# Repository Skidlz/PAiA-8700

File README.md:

# PAiA-8700
A redraw of the PAiA 8700 music computer in Eagle CAD</br>
Also includes:</br>
 - Python scripts for converting to and from tape dump format

 ##### TAPE PROGRAMS #####
 - [**Echo**](Tape%20Programs/Echo/) listing/binary/tape dump
 - [**Orgasmatronic Glide (O-Glide)**](Tape%20Programs/O-Glide) listing/binary/tape dump
 - [**Poly-Split**](Tape%20Programs/Poly-Split/) listing/binary/tape dump
 - [**Poly**](Tape%20Programs/Poly/) listing/source/binary/audio file
 - [**Seque**](Tape%20Programs/Seque/) listing/binary/tape dump
 - [**Pink Tunes**](Tape%20Programs/Pink%20Tunes/) listing/source/binary/tape dump
 - [**Pink Music**](Tape%20Programs/Pink%20Music/) listing/source/binary/audio file
 - [**DrumSys 0.6**](Tape%20Programs/DRUMSYS%2006/) listing/source/binary/audio file
 - [**Shazam 0.1**](Tape%20Programs/SHAZAM/) listing/source/binary/audio file
 - [**Micro-Drums 2.1**](Tape%20Programs/Micro-Drums/) listing/source/binary/audio file
 - [**Chameleon**](Tape%20Programs/Chameleon) listing/source/binary
 - Test programs source/binary/tape dump

##### EPROM PROGRAMS #####
 - [**PIEBUG**](EPROM%20Programs/PIEBUG) listing/binary/source
 - [**POT-SHOT**](EPROM%20Programs/POT-SHOT) listing/binary/source
 - [**MUS-1**](EPROM%20Programs/MUS-1) listing/source/binary
 
##### EXTRAS #####
 - memory map
 
 - 600DPI scan on the Seque overlay

##### NOTES #####
.asm files can be assembled with [Frank's Cross Assembler (AS65)](http://www.kingswood-consulting.co.uk/assemblers/).

##### BUGS #####
###### DrumSys ######
The original code listing for DrumSys contains an error in the code/data alginment. Two versions are included here, and they correct the error in opposite ways. One shifts the data, while the other shifts the code.

###### Echo ######
Echo has a relative branch that is out of range. At address $080 is "beq STAR". STAR, being at $000, is a byte too far away, and the branch instead points to $100. This has not been corrected. Adding a "jmp STAR" at address $100 is a possible fix to the issue.

.jpg)

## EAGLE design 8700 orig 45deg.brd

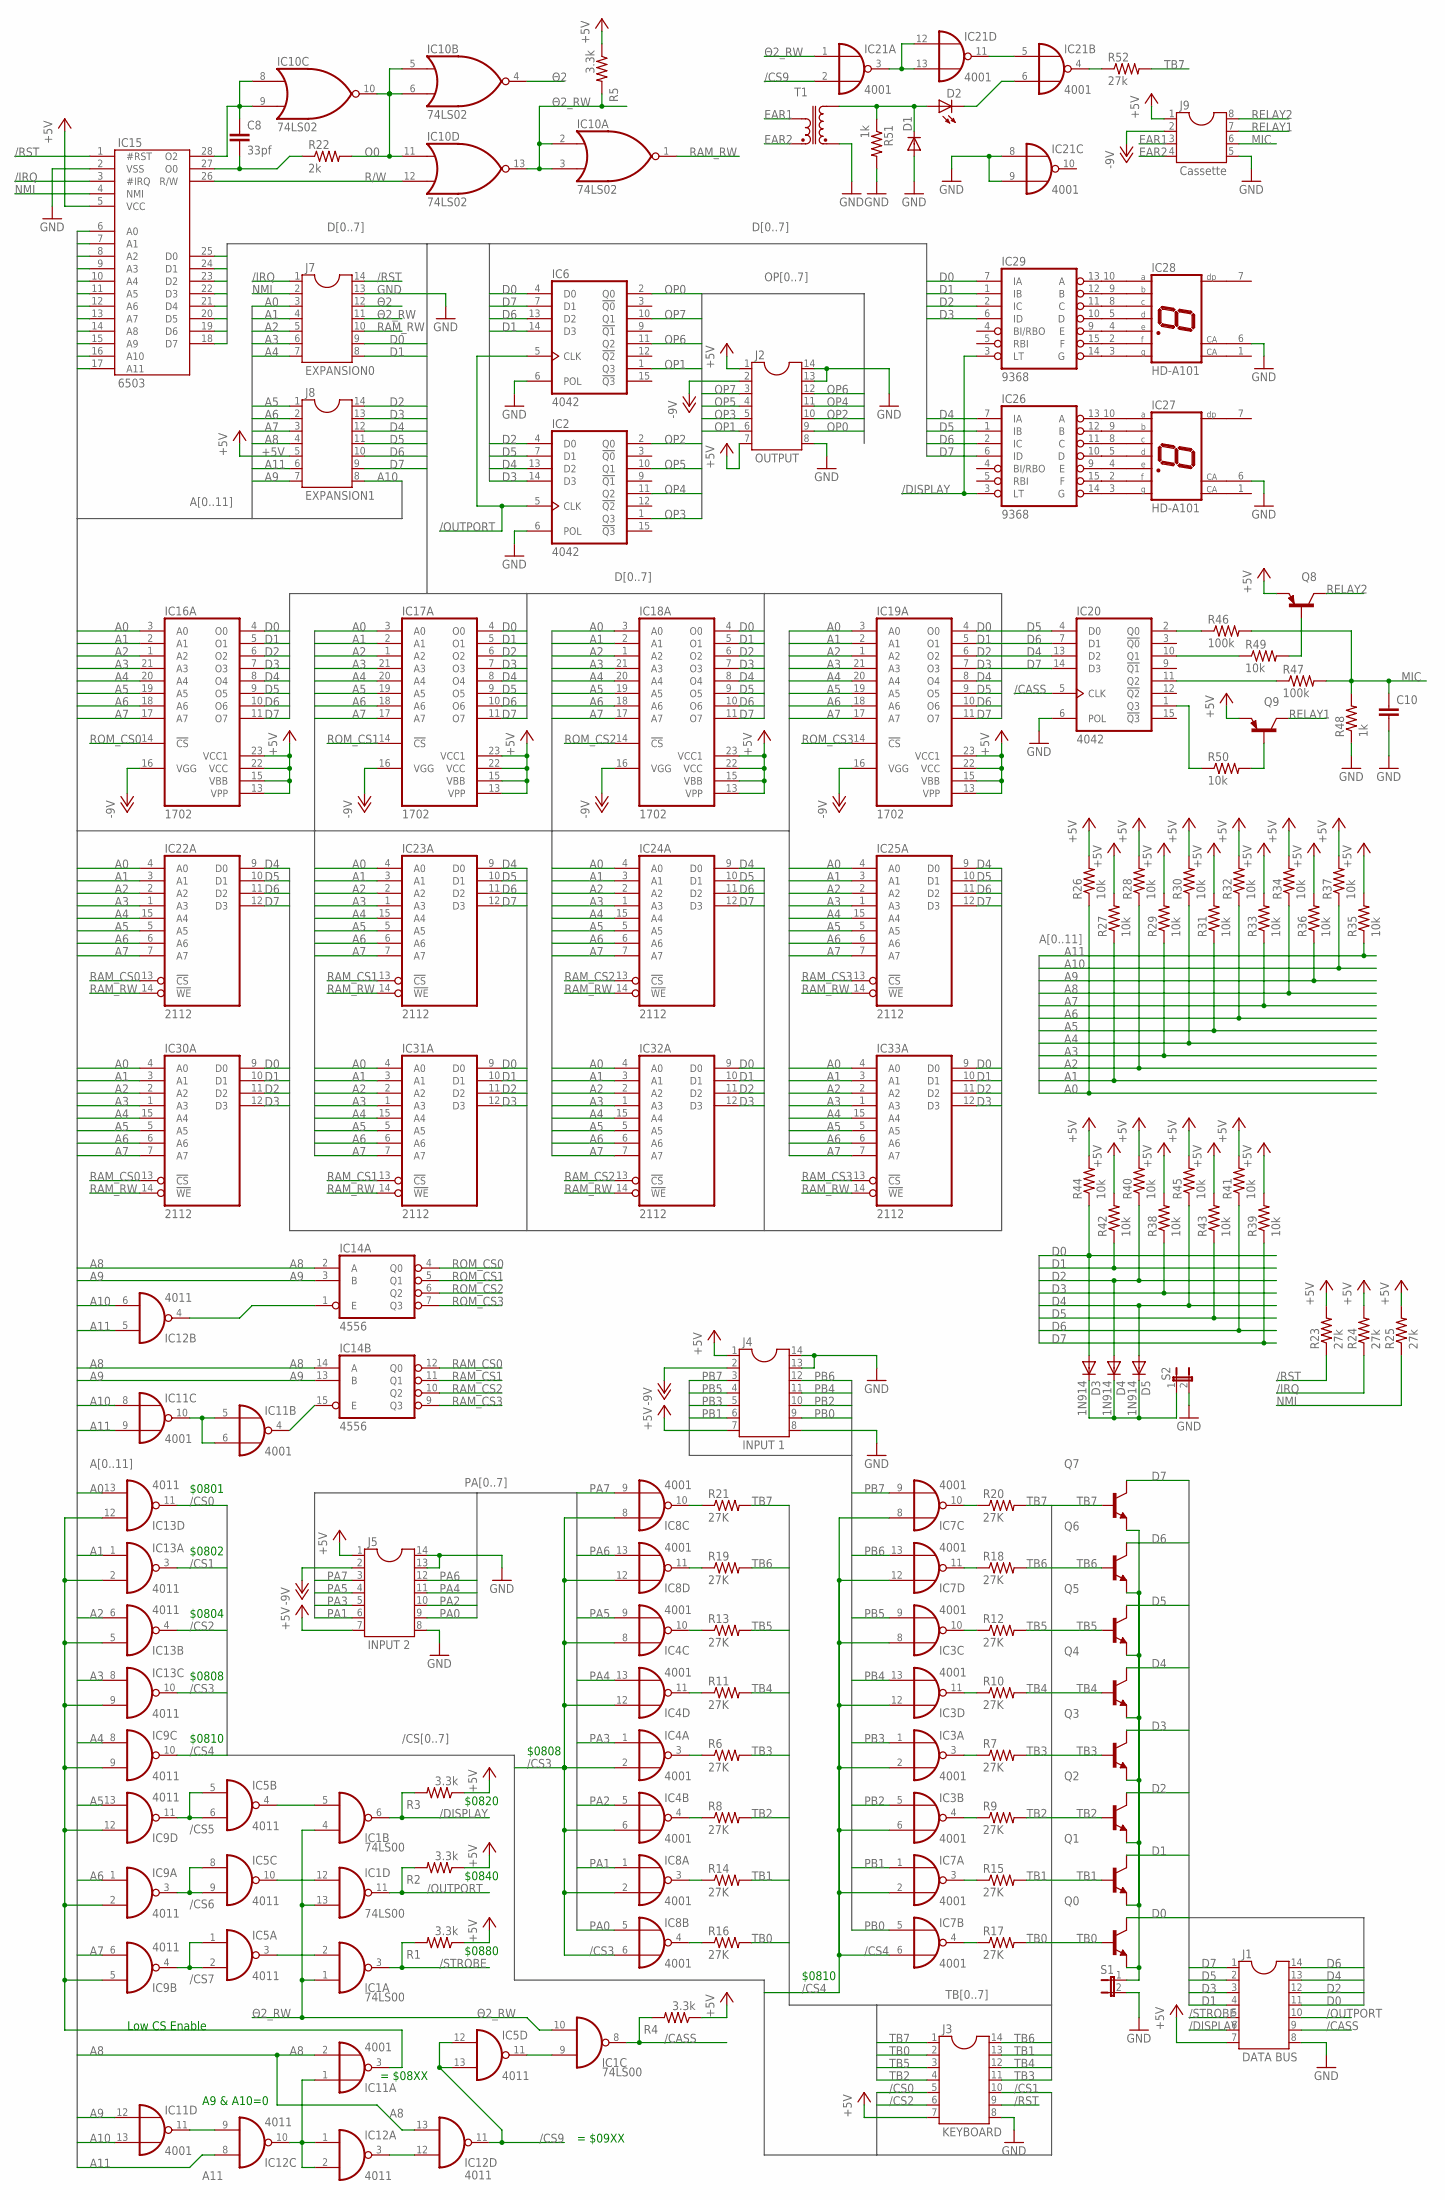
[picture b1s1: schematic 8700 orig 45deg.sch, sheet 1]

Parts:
C8: 33pf; C050-025X075
C10: C-EU050-025X075; C050-025X075
D1: DIODE-DO07; DO07
D2: LED3MM
D3, D4, D5: 1N914; DO07
IC1: 74LS00; DIL14
IC2, IC6, IC20: 4042; DIL16
IC3, IC4, IC7, IC8, IC11, IC21: 4001; DIL14
IC5, IC9, IC12, IC13: 4011; DIL14
IC10: 74LS02; DIL14
IC14: 4556; DIL16
IC15: 6503; DIL28-6
IC16, IC17, IC18, IC19: 1702; DIL24
IC22, IC23, IC24, IC25, IC30, IC31, IC32, IC33: 2112; DIL16
IC26, IC29: 9368; DIL16
IC27, IC28: HD-A101; HDSP-A
J1: DATA BUS; DIL14
J2: OUTPUT; DIL14
J3: KEYBOARD; DIL14
J4: INPUT 1; DIL14
J5: INPUT 2; DIL14
J7: EXPANSION0; DIL14
J8: EXPANSION1; DIL14
J9: Cassette; DIL08
Q0, Q1, Q2, Q3, Q4, Q5, Q6, Q7: 2N3904-NPN-TO92-EBC; TO92-EBC
Q8, Q9: 2N3906-PNP-TO92-EBC; TO92-EBC
R1, R2, R3, R4, R5: 3.3k; 0207/10
R6, R7, R8, R9, R10, R11, R12, R13, R14, R15, R16, R17, R18, R19, R20, R21: 27K; 0207/10
R22: 2k; 0207/10
R23, R24, R25, R52: 27k; 0207/10
R26, R27, R28, R29, R30, R31, R32, R33, R34, R35, R36, R37, R38, R39, R40, R41, R42, R43, R44, R45, R49, R50: 10k; 0207/10
R46, R47: 100k; 0207/10
R48, R51: 1k; 0207/10
S1, S2: JUMPER
T1: TRANSF

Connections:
+5V: IC15.5 (VCC), IC16.13 (VPP), IC16.15 (VBB), IC16.22 (VCC), IC16.23 (VCC1), IC17.13 (VPP), IC17.15 (VBB), IC17.22 (VCC), IC17.23 (VCC1), IC18.13 (VPP), IC18.15 (VBB), IC18.22 (VCC), IC18.23 (VCC1), IC19.13 (VPP), IC19.15 (VBB), IC19.22 (VCC), IC19.23 (VCC1), J1.7, J2.1, J2.7, J3.7, J4.1, J4.7, J5.1, J5.7, J8.5, J9.1, Q8.E, Q9.E, R1.1, R2.1, R3.1, R4.1, R5.1, R23.2, R24.2, R25.2, R26.2, R27.2, R28.2, R29.2, R30.2, R31.2, R32.2, R33.2, R34.2, R35.2, R36.2, R37.2, R38.2, R39.2, R40.2, R41.2, R42.2, R43.2, R44.2, R45.2; also elsewhere on the board
-9V: IC16.16 (VGG), IC17.16 (VGG), IC18.16 (VGG), IC19.16 (VGG), J2.2, J4.2, J5.2, J9.2; also elsewhere on the board
/CASS: IC1.8 (O), IC20.5 (CLK), J1.9, R4.2
/CS0: IC13.11 (O), J3.5
/CS1: IC13.3 (O), J3.10
/CS2: IC13.4 (O), J3.6
/CS3: IC4.2 (I1), IC4.6 (I1), IC4.8 (I0), IC4.12 (I0), IC8.2 (I1), IC8.6 (I1), IC8.8 (I0), IC8.12 (I0), IC13.10 (O)
/CS4: IC3.2 (I1), IC3.6 (I1), IC3.8 (I0), IC3.12 (I0), IC7.2 (I1), IC7.6 (I1), IC7.8 (I0), IC7.12 (I0), IC9.10 (O)
/CS5: IC5.5 (I0), IC5.6 (I1), IC9.11 (O)
/CS6: IC5.8 (I0), IC5.9 (I1), IC9.3 (O)
/CS7: IC5.1 (I0), IC5.2 (I1), IC9.4 (O)
/CS9: IC5.12 (I0), IC5.13 (I1), IC12.11 (O), IC21.2 (I1)
/DISPLAY: IC1.6 (O), IC26.3 (LT), IC29.3 (LT), J1.6, R3.2
/IRQ: IC15.3 (#IRQ), J7.1, R24.1
/OUTPORT: IC1.11 (O), IC2.5 (CLK), IC6.5 (CLK), J1.10, R2.2
/RST: IC15.1 (#RST), J3.9, J7.14, R23.1
/STROBE: IC1.3 (O), J1.5, R1.2
A0: IC13.13 (I1), IC15.6 (A0), IC16.3 (A0), IC17.3 (A0), IC18.3 (A0), IC19.3 (A0), IC22.4 (A0), IC23.4 (A0), IC24.4 (A0), IC25.4 (A0), IC30.4 (A0), IC31.4 (A0), IC32.4 (A0), IC33.4 (A0), J7.3, R26.1
A1: IC13.1 (I0), IC15.7 (A1), IC16.2 (A1), IC17.2 (A1), IC18.2 (A1), IC19.2 (A1), IC22.3 (A1), IC23.3 (A1), IC24.3 (A1), IC25.3 (A1), IC30.3 (A1), IC31.3 (A1), IC32.3 (A1), IC33.3 (A1), J7.4, R27.1
A2: IC13.6 (I1), IC15.8 (A2), IC16.1 (A2), IC17.1 (A2), IC18.1 (A2), IC19.1 (A2), IC22.2 (A2), IC23.2 (A2), IC24.2 (A2), IC25.2 (A2), IC30.2 (A2), IC31.2 (A2), IC32.2 (A2), IC33.2 (A2), J7.5, R28.1
A3: IC13.8 (I0), IC15.9 (A3), IC16.21 (A3), IC17.21 (A3), IC18.21 (A3), IC19.21 (A3), IC22.1 (A3), IC23.1 (A3), IC24.1 (A3), IC25.1 (A3), IC30.1 (A3), IC31.1 (A3), IC32.1 (A3), IC33.1 (A3), J7.6, R29.1
A4: IC9.8 (I0), IC15.10 (A4), IC16.20 (A4), IC17.20 (A4), IC18.20 (A4), IC19.20 (A4), IC22.15 (A4), IC23.15 (A4), IC24.15 (A4), IC25.15 (A4), IC30.15 (A4), IC31.15 (A4), IC32.15 (A4), IC33.15 (A4), J7.7, R30.1
A5: IC9.13 (I1), IC15.11 (A5), IC16.19 (A5), IC17.19 (A5), IC18.19 (A5), IC19.19 (A5), IC22.5 (A5), IC23.5 (A5), IC24.5 (A5), IC25.5 (A5), IC30.5 (A5), IC31.5 (A5), IC32.5 (A5), IC33.5 (A5), J8.1, R31.1
A6: IC9.1 (I0), IC15.12 (A6), IC16.18 (A6), IC17.18 (A6), IC18.18 (A6), IC19.18 (A6), IC22.6 (A6), IC23.6 (A6), IC24.6 (A6), IC25.6 (A6), IC30.6 (A6), IC31.6 (A6), IC32.6 (A6), IC33.6 (A6), J8.2, R32.1
A7: IC9.6 (I1), IC15.13 (A7), IC16.17 (A7), IC17.17 (A7), IC18.17 (A7), IC19.17 (A7), IC22.7 (A7), IC23.7 (A7), IC24.7 (A7), IC25.7 (A7), IC30.7 (A7), IC31.7 (A7), IC32.7 (A7), IC33.7 (A7), J8.3, R33.1
A8: IC11.2 (I1), IC12.13 (I1), IC14.2 (A), IC14.14 (A), IC15.14 (A8), J8.4, R34.1
A9: IC11.12 (I0), IC14.3 (B), IC14.13 (B), IC15.15 (A9), J8.7, R36.1
A10: IC11.8 (I0), IC11.13 (I1), IC12.6 (I1), IC15.16 (A10), J8.8, R37.1
A11: IC11.9 (I1), IC12.5 (I0), IC12.8 (I0), IC15.17 (A11), J8.6, R35.1
D0: D3.A, IC6.4 (D0), IC15.25 (D0), IC16.4 (O0), IC17.4 (O0), IC18.4 (O0), IC19.4 (O0), IC29.7 (IA), IC30.9 (D0), IC31.9 (D0), IC32.9 (D0), IC33.9 (D0), J1.11, J7.9, Q0.C, R44.1
D1: IC6.14 (D3), IC15.24 (D1), IC16.5 (O1), IC17.5 (O1), IC18.5 (O1), IC19.5 (O1), IC29.1 (IB), IC30.10 (D1), IC31.10 (D1), IC32.10 (D1), IC33.10 (D1), J1.4, J7.8, Q1.C, R42.1
D2: D4.A, IC2.4 (D0), IC15.23 (D2), IC16.6 (O2), IC17.6 (O2), IC18.6 (O2), IC19.6 (O2), IC29.2 (IC), IC30.11 (D2), IC31.11 (D2), IC32.11 (D2), IC33.11 (D2), J1.12, J8.14, Q2.C, R40.1
D3: IC2.14 (D3), IC15.22 (D3), IC16.7 (O3), IC17.7 (O3), IC18.7 (O3), IC19.7 (O3), IC29.6 (ID), IC30.12 (D3), IC31.12 (D3), IC32.12 (D3), IC33.12 (D3), J1.3, J8.13, Q3.C, R38.1
D4: D5.A, IC2.13 (D2), IC15.21 (D4), IC16.8 (O4), IC17.8 (O4), IC18.8 (O4), IC19.8 (O4), IC20.13 (D2), IC22.9 (D0), IC23.9 (D0), IC24.9 (D0), IC25.9 (D0), IC26.7 (IA), J1.13, J8.12, Q4.C, R45.1
D5: IC2.7 (D1), IC15.20 (D5), IC16.9 (O5), IC17.9 (O5), IC18.9 (O5), IC19.9 (O5), IC20.4 (D0), IC22.10 (D1), IC23.10 (D1), IC24.10 (D1), IC25.10 (D1), IC26.1 (IB), J1.2, J8.11, Q5.C, R43.1
D6: IC6.13 (D2), IC15.19 (D6), IC16.10 (O6), IC17.10 (O6), IC18.10 (O6), IC19.10 (O6), IC20.7 (D1), IC22.11 (D2), IC23.11 (D2), IC24.11 (D2), IC25.11 (D2), IC26.2 (IC), J1.14, J8.10, Q6.C, R41.1
D7: IC6.7 (D1), IC15.18 (D7), IC16.11 (O7), IC17.11 (O7), IC18.11 (O7), IC19.11 (O7), IC20.14 (D3), IC22.12 (D3), IC23.12 (D3), IC24.12 (D3), IC25.12 (D3), IC26.6 (ID), J1.1, J8.9, Q7.C, R39.1
EAR1: J9.3, T1.P$1 (P1)
EAR2: J9.4, T1.P$2 (P2)
GND: C10.2, D1.A, IC2.6 (POL), IC6.6 (POL), IC15.2 (VSS), IC20.6 (POL), IC21.8 (I0), IC21.9 (I1), IC27.6 (CA), IC28.6 (CA), J1.8, J2.8, J2.13, J2.14, J3.8, J4.8, J4.13, J4.14, J5.8, J5.13, J5.14, J7.13, J9.5, R48.1, R51.2, S1.2, S2.2, T1.P$5 (S1); also elsewhere on the board
MIC: C10.1, J9.6, R46.2, R47.2, R48.2
unnamed: C8.1, IC10.8 (I0), IC10.9 (I1), IC15.28 (O2)
unnamed: IC21.3 (O), IC21.12 (I0), IC21.13 (I1)
unnamed: C8.2, IC15.27 (O0), R22.1
unnamed: D2.K (C), IC21.6 (I1)
unnamed: IC21.5 (I0), IC21.11 (O)
unnamed: IC21.4 (O), R52.1
unnamed: Q0.E, Q1.E, Q2.E, Q3.E, Q4.E, Q5.E, Q6.E, Q7.E, S1.1
unnamed: IC9.2 (I1), IC9.5 (I0), IC9.9 (I1), IC9.12 (I0), IC11.3 (O), IC13.2 (I1), IC13.5 (I0), IC13.9 (I1), IC13.12 (I0)
unnamed: IC1.2 (I1), IC5.3 (O)
unnamed: IC1.5 (I1), IC5.4 (O)
unnamed: IC12.4 (O), IC14.1 (E)
unnamed: IC11.5 (I0), IC11.6 (I1), IC11.10 (O)
unnamed: IC1.12 (I0), IC5.10 (O)
unnamed: IC11.4 (O), IC14.15 (E)
unnamed: IC11.11 (O), IC12.9 (I1)
unnamed: IC11.1 (I0), IC12.1 (I0), IC12.2 (I1), IC12.10 (O)
unnamed: IC12.3 (O), IC12.12 (I0)
unnamed: IC1.9 (I0), IC5.11 (O)
unnamed: IC8.3 (O), R14.1
unnamed: IC8.4 (O), R16.1
unnamed: IC20.11 (Q2), R47.1
unnamed: IC4.4 (O), R8.1
unnamed: IC4.3 (O), R6.1
unnamed: IC4.11 (O), R11.1
unnamed: IC4.10 (O), R13.1
unnamed: IC8.11 (O), R19.1
unnamed: IC8.10 (O), R21.1
unnamed: IC7.4 (O), R17.1
unnamed: IC7.3 (O), R15.1
unnamed: IC3.4 (O), R9.1
unnamed: IC3.3 (O), R7.1
unnamed: IC3.11 (O), R10.1
unnamed: IC3.10 (O), R12.1
unnamed: IC7.11 (O), R18.1
unnamed: IC7.10 (O), R20.1
unnamed: IC20.1 (Q3), R50.1
unnamed: IC28.2 (F), IC29.15 (F)
unnamed: IC28.5 (D), IC29.10 (D)
unnamed: Q9.B, R50.2
unnamed: Q8.B, R49.2
unnamed: IC28.9 (B), IC29.12 (B)
unnamed: IC28.10 (A), IC29.13 (A)
unnamed: IC20.2 (Q0), R46.1
unnamed: IC20.10 (Q1), R49.1
unnamed: IC28.8 (C), IC29.11 (C)
unnamed: IC28.4 (E), IC29.9 (E)
unnamed: IC28.3 (G), IC29.14 (G)
unnamed: IC26.15 (F), IC27.2 (F)
unnamed: IC26.10 (D), IC27.5 (D)
unnamed: IC26.12 (B), IC27.9 (B)
unnamed: IC26.13 (A), IC27.10 (A)
unnamed: IC26.11 (C), IC27.8 (C)
unnamed: IC26.9 (E), IC27.4 (E)
unnamed: IC26.14 (G), IC27.3 (G)
unnamed: D3.C, D4.C, D5.C, S2.1
unnamed: D1.C, D2.A, R51.1, T1.P$3 (S2)
NMI: IC15.4 (NMI), J7.2, R25.1
O0: IC10.5 (I0), IC10.6 (I1), IC10.10 (O), IC10.11 (I0), R22.2
OP0: IC6.2 (Q0), J2.9
OP1: IC6.1 (Q3), J2.6
OP2: IC2.2 (Q0), J2.10
OP3: IC2.1 (Q3), J2.5
OP4: IC2.11 (Q2), J2.11
OP5: IC2.10 (Q1), J2.4
OP6: IC6.11 (Q2), J2.12
OP7: IC6.10 (Q1), J2.3
PA0: IC8.5 (I0), J5.9
PA1: IC8.1 (I0), J5.6
PA2: IC4.5 (I0), J5.10
PA3: IC4.1 (I0), J5.5
PA4: IC4.13 (I1), J5.11
PA5: IC4.9 (I1), J5.4
PA6: IC8.13 (I1), J5.12
PA7: IC8.9 (I1), J5.3
PB0: IC7.5 (I0), J4.9
PB1: IC7.1 (I0), J4.6
PB2: IC3.5 (I0), J4.10
PB3: IC3.1 (I0), J4.5
PB4: IC3.13 (I1), J4.11
PB5: IC3.9 (I1), J4.4
PB6: IC7.13 (I1), J4.12
PB7: IC7.9 (I1), J4.3
R/W: IC10.12 (I1), IC15.26 (R/W)
RAM_CS0: IC14.12 (Q0), IC22.13 (!CS), IC30.13 (!CS)
RAM_CS1: IC14.11 (Q1), IC23.13 (!CS), IC31.13 (!CS)
RAM_CS2: IC14.10 (Q2), IC24.13 (!CS), IC32.13 (!CS)
RAM_CS3: IC14.9 (Q3), IC25.13 (!CS), IC33.13 (!CS)
RAM_RW: IC10.1 (O), IC22.14 (!WE), IC23.14 (!WE), IC24.14 (!WE), IC25.14 (!WE), IC30.14 (!WE), IC31.14 (!WE), IC32.14 (!WE), IC33.14 (!WE), J7.10
RELAY1: J9.7, Q9.C
RELAY2: J9.8, Q8.C
ROM_CS0: IC14.4 (Q0), IC16.14 (!CS)
ROM_CS1: IC14.5 (Q1), IC17.14 (!CS)
ROM_CS2: IC14.6 (Q2), IC18.14 (!CS)
ROM_CS3: IC14.7 (Q3), IC19.14 (!CS)
TB0: J3.2, Q0.B, R16.2, R17.2
TB1: J3.13, Q1.B, R14.2, R15.2
TB2: J3.4, Q2.B, R8.2, R9.2
TB3: J3.11, Q3.B, R6.2, R7.2
TB4: J3.12, Q4.B, R10.2, R11.2
TB5: J3.3, Q5.B, R12.2, R13.2
TB6: J3.14, Q6.B, R18.2, R19.2
TB7: J3.1, Q7.B, R20.2, R21.2, R52.2
Θ2: IC10.4 (O), J7.12
Θ2_RW: IC1.1 (I0), IC1.4 (I0), IC1.10 (I1), IC1.13 (I1), IC10.2 (I0), IC10.3 (I1), IC10.13 (O), IC21.1 (I0), J7.11, R5.2

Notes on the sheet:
Low CS Enable
A9 & A10=0
= $09XX
= $08XX
$0820
$0840
$0880
$0810
$0808
$0804
$0802
$0801

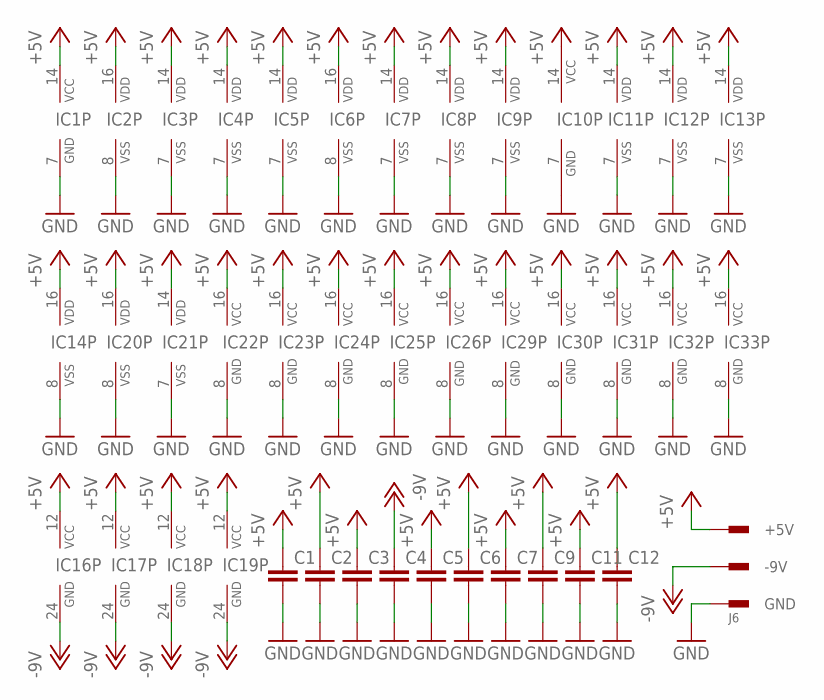
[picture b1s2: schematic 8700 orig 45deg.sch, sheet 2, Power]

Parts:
C1, C2, C3, C4, C5, C6, C7, C9, C11, C12: C-EU050-025X075; C050-025X075
IC1: 74LS00; DIL14
IC2, IC6, IC20: 4042; DIL16
IC3, IC4, IC7, IC8, IC11, IC21: 4001; DIL14
IC5, IC9, IC12, IC13: 4011; DIL14
IC10: 74LS02; DIL14
IC14: 4556; DIL16
IC16, IC17, IC18, IC19: 1702; DIL24
IC22, IC23, IC24, IC25, IC30, IC31, IC32, IC33: 2112; DIL16
IC26, IC29: 9368; DIL16
J6: POWER

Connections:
+5V: C1.1, C2.1, C3.1, C5.1, C6.1, C7.1, C9.1, C11.1, C12.1, IC1.14 (VCC), IC2.16 (VDD), IC3.14 (VDD), IC4.14 (VDD), IC5.14 (VDD), IC6.16 (VDD), IC7.14 (VDD), IC8.14 (VDD), IC9.14 (VDD), IC10.14 (VCC), IC11.14 (VDD), IC12.14 (VDD), IC13.14 (VDD), IC14.16 (VDD), IC16.12 (VCC), IC17.12 (VCC), IC18.12 (VCC), IC19.12 (VCC), IC20.16 (VDD), IC21.14 (VDD), IC22.16 (VCC), IC23.16 (VCC), IC24.16 (VCC), IC25.16 (VCC), IC26.16 (VCC), IC29.16 (VCC), IC30.16 (VCC), IC31.16 (VCC), IC32.16 (VCC), IC33.16 (VCC), J6.P$1 (+5V); also elsewhere on the board
-9V: C4.1, IC16.24 (GND), IC17.24 (GND), IC18.24 (GND), IC19.24 (GND), J6.P$2 (-9V); also elsewhere on the board
GND: C1.2, C2.2, C3.2, C4.2, C5.2, C6.2, C7.2, C9.2, C11.2, C12.2, IC1.7 (GND), IC2.8 (VSS), IC3.7 (VSS), IC4.7 (VSS), IC5.7 (VSS), IC6.8 (VSS), IC7.7 (VSS), IC8.7 (VSS), IC9.7 (VSS), IC10.7 (GND), IC11.7 (VSS), IC12.7 (VSS), IC13.7 (VSS), IC14.8 (VSS), IC20.8 (VSS), IC21.7 (VSS), IC22.8 (GND), IC23.8 (GND), IC24.8 (GND), IC25.8 (GND), IC26.8 (GND), IC29.8 (GND), IC30.8 (GND), IC31.8 (GND), IC32.8 (GND), IC33.8 (GND), J6.P$3 (GND); also elsewhere on the board

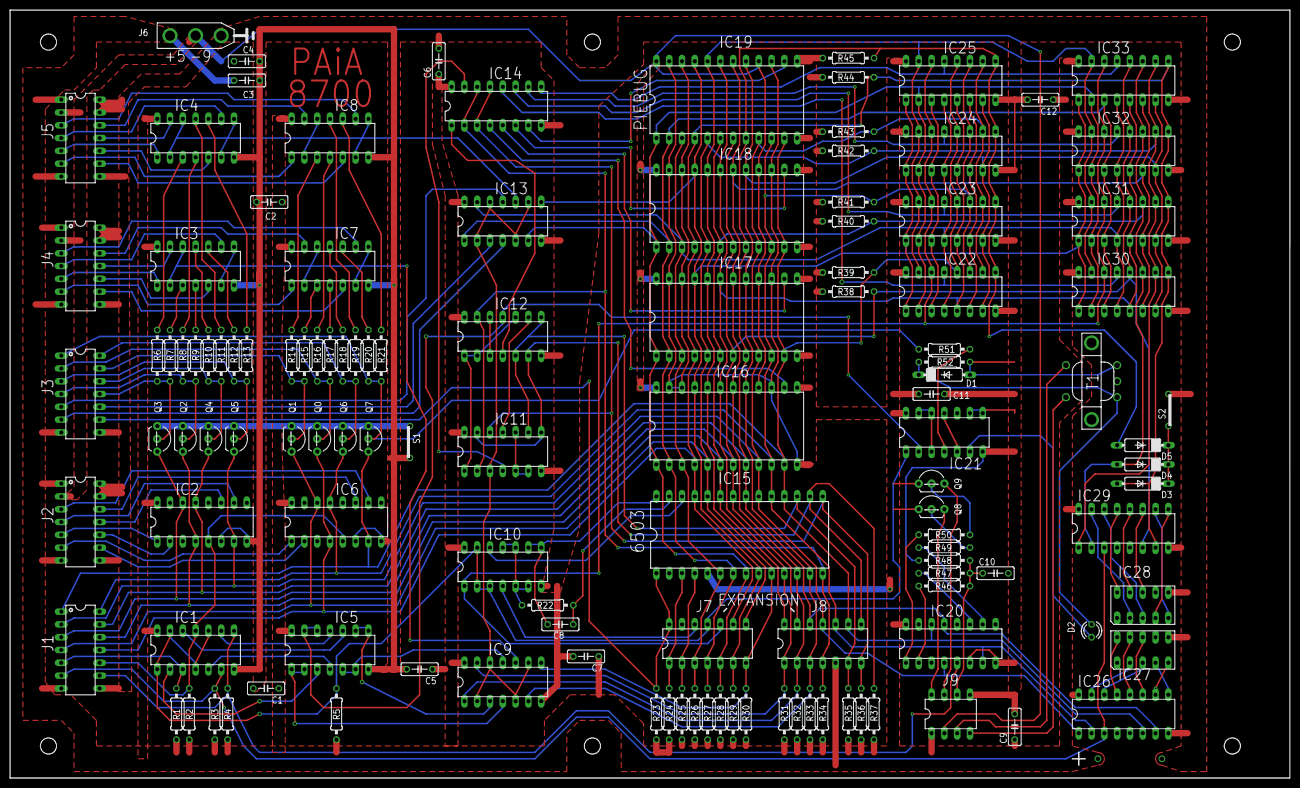
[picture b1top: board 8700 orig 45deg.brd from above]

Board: 2 copper layers, 254.0 x 152.4 mm, 124 parts (0 on the bottom side), 145 nets.

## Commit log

2019-02-17 Initial upload
2019-02-17 Uploading PIEBUG binary and source
2019-02-18 Uploading images
2019-02-18 Uploading memory map
2020-05-26 Fixed wrong byte
2020-05-27 Added binary files
2020-10-18 Added tape tools/programs. Assemble with as65
2020-12-10 Added tape dumps, binary files, and code listings
2021-11-22 Added updated scripts
2021-11-22 Added DrumSys 0.6
2021-11-22 Moved binary files
2022-03-04 Added SHAZAM 0.1
2022-03-04 Adding Poly
2022-03-06 Added Pink Music
2022-03-09 Added MUS-1 assembly source (commented)
2022-04-06 Fixing 'result' address typo
2022-04-25 Adding Poly-Split comments and assembly file
2025-03-22 Adding Micro-Drums 2.1
2025-04-03 Adding Micro Drums scan
2025-04-03 Adding Shazam scan
2025-04-03 Adding Pink Music scan
2025-04-03 Adding O-Glide scan
2025-04-03 Adding MUS1 scan
2025-04-03 Adding Echo scan
2025-04-03 Adding Pink Tunes scan
2025-04-03 Adding Poly-Split scan
2025-04-03 Adding Seque scan
2025-04-03 Adding Poly scan
2025-04-03 Adding DrumSys scan
2025-04-20 Adding PIEBUG scan
2025-04-20 Adding POT-SHOT scan
2025-04-20 Updating PIEBUG
2025-04-20 Update POT-SHOT
2025-04-26 Update MUS-1 & Pink Tunes
2025-04-26 Adding Chameleon
2025-05-09 Update KTEST
2025-05-10 Better Shazam scan
2025-05-10 Adding another Seque scan, plus real source, listing, and bin
2025-05-10 Fixing Drumsys lda bug
2025-05-10 Updating Drumsys and Quash Test
2025-05-13 Fix MUS-1 typos
2025-05-13 Updating Echo
2025-05-15 Adding proper Poly scan/source/listing
2025-05-15 Poly cleanup
2025-05-15 Update Pink Music
2025-05-15 Update O-Glide
2025-05-15 Update Shazam
2025-05-16 Update Pink Tunes
2025-05-16 Update Seque
2025-05-16 Update Poly-Split
